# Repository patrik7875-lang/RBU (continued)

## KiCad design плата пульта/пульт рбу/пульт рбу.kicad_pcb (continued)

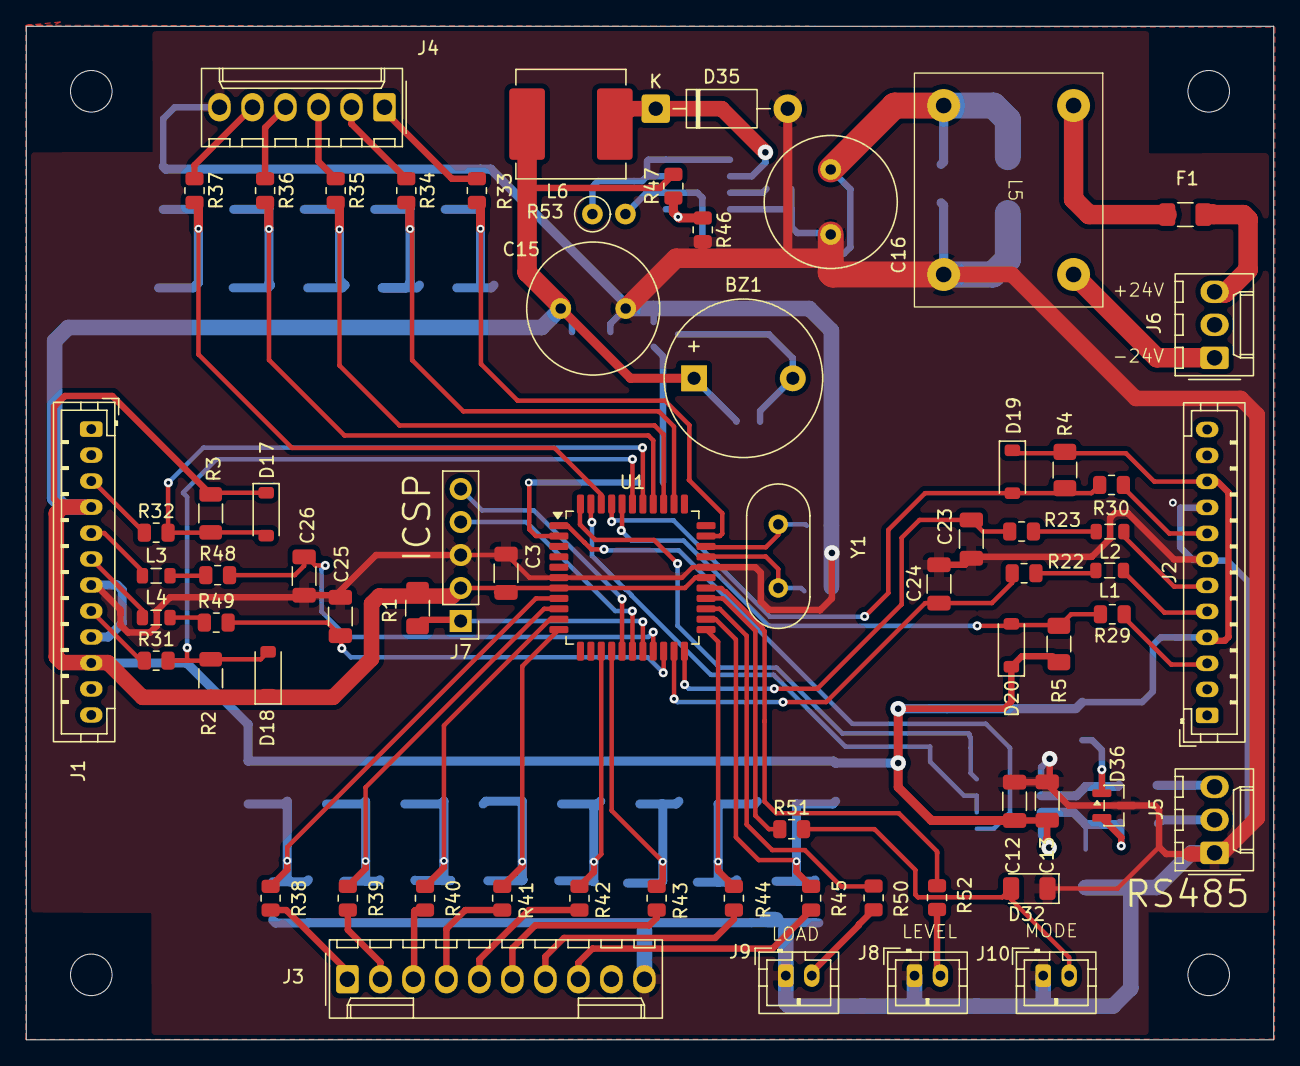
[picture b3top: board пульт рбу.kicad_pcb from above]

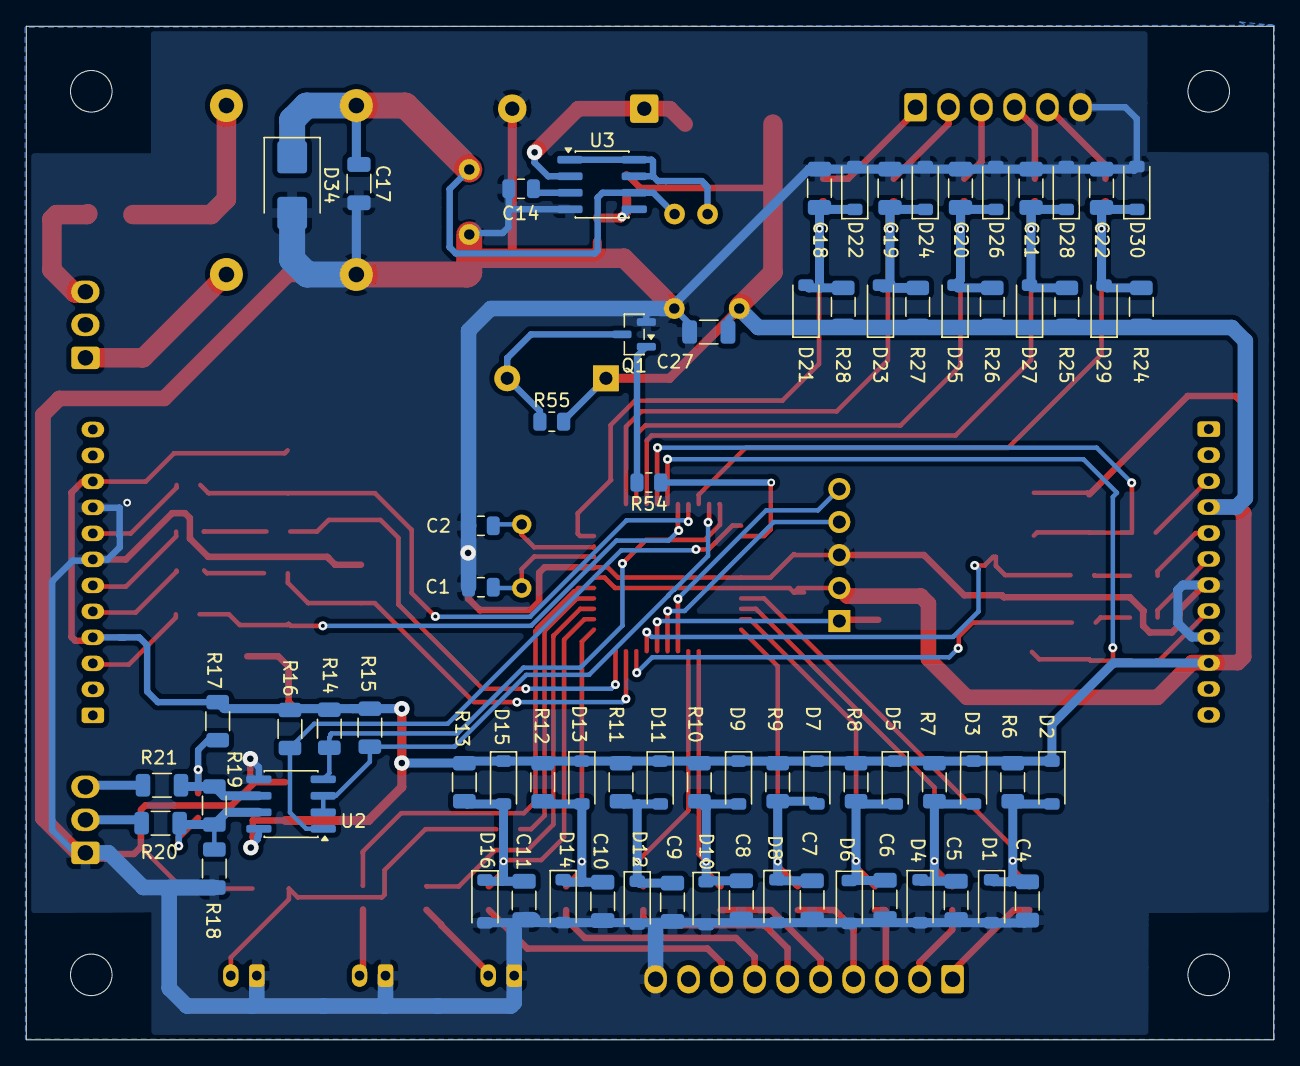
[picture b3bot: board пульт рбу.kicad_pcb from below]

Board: 2 copper layers, 96.0 x 78.0 mm, 139 parts (71 on the bottom side), 77 nets.
